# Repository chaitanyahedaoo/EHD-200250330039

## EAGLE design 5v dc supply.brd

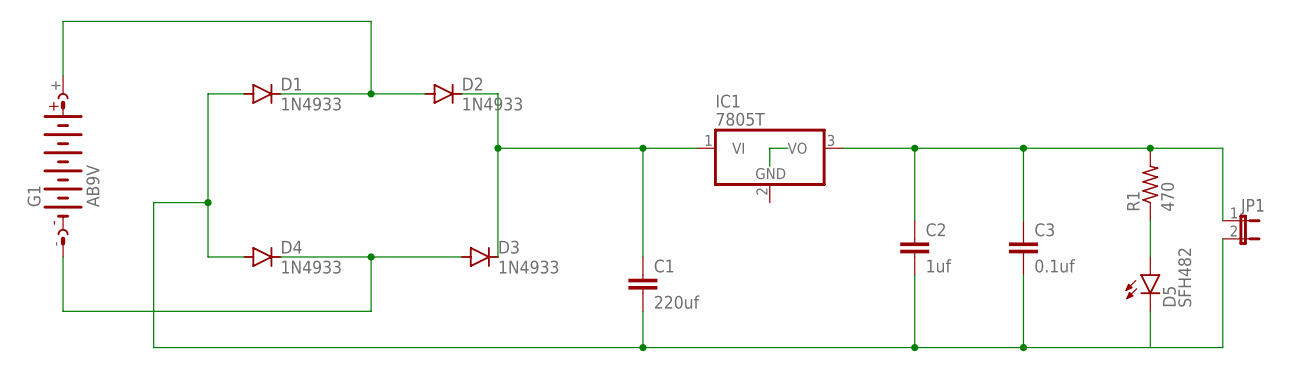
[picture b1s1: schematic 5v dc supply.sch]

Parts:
C1: 220uf; C2.5-3
C2: 1uf; C2.5-3
C3: 0.1uf; C2.5-3
D1, D2, D3, D4: 1N4933; DO41-10
D5: SFH482
G1: AB9V
IC1: 7805T; TO220H
JP1: JP1E; JP1
R1: 470; 0204/7

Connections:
unnamed: D5.A, R1.1
unnamed: C1.2, C2.2, C3.2, D1.A, D4.A, D5.K (C), JP1.2
unnamed: D3.A, D4.C, G1.-
unnamed: C1.1, D2.C, D3.C, IC1.1 (VI)
unnamed: D1.C, D2.A, G1.+
unnamed: C2.1, C3.1, IC1.3 (VO), JP1.1, R1.2

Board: 2 copper layers, 12 parts (0 on the bottom side), 6 nets, no tracks yet.

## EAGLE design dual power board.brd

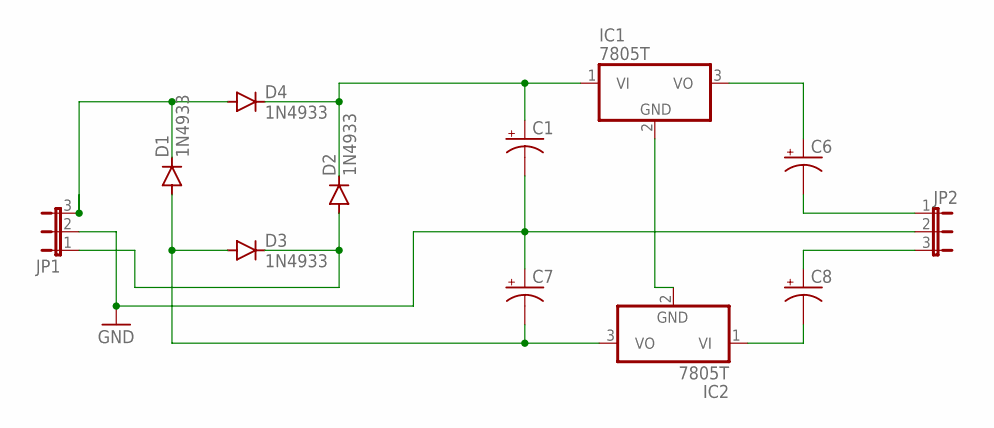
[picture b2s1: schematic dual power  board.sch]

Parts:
C1, C6, C7, C8: CPOL-USE5-5; E5-5
D1, D2, D3, D4: 1N4933; DO41-10
IC1, IC2: 7805T; TO220H
JP1, JP2: JP2E; JP2

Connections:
unnamed: D1.C, D4.A, JP1.3
unnamed: C6.-, JP2.1
unnamed: D2.A, D3.C, JP1.1
unnamed: C8.+, JP2.3
unnamed: C1.+, D2.C, D4.C, IC1.1 (VI)
unnamed: C6.+, IC1.3 (VO)
unnamed: IC1.2 (GND), IC2.2 (GND)
unnamed: C1.-, C7.+, JP1.2, JP2.2
unnamed: C8.-, IC2.1 (VI)
unnamed: C7.-, D1.A, D3.A, IC2.3 (VO)

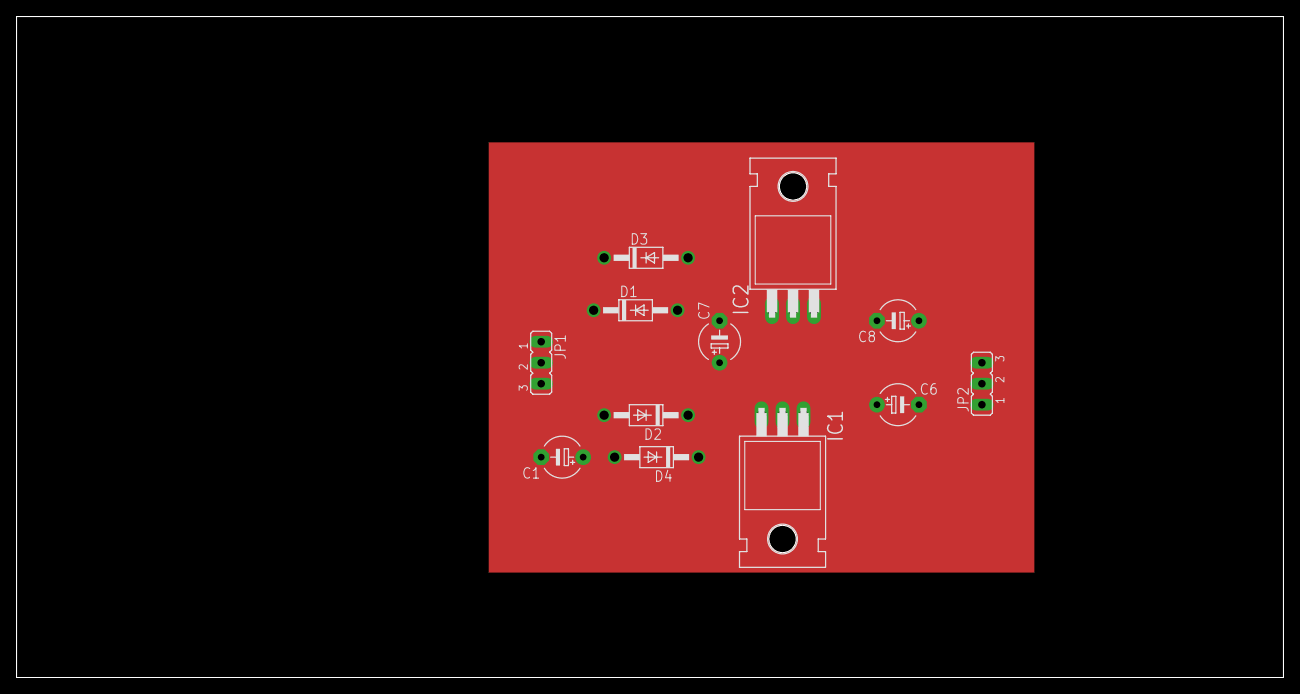
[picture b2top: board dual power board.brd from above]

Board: 2 copper layers, 153.3 x 80.0 mm, 12 parts (0 on the bottom side), 10 nets.
